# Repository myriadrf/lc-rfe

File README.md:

#  LibreCellular RFE Hardware

This repository contains the KiCAD design and manufacturing files for the LC-RFE hardware.

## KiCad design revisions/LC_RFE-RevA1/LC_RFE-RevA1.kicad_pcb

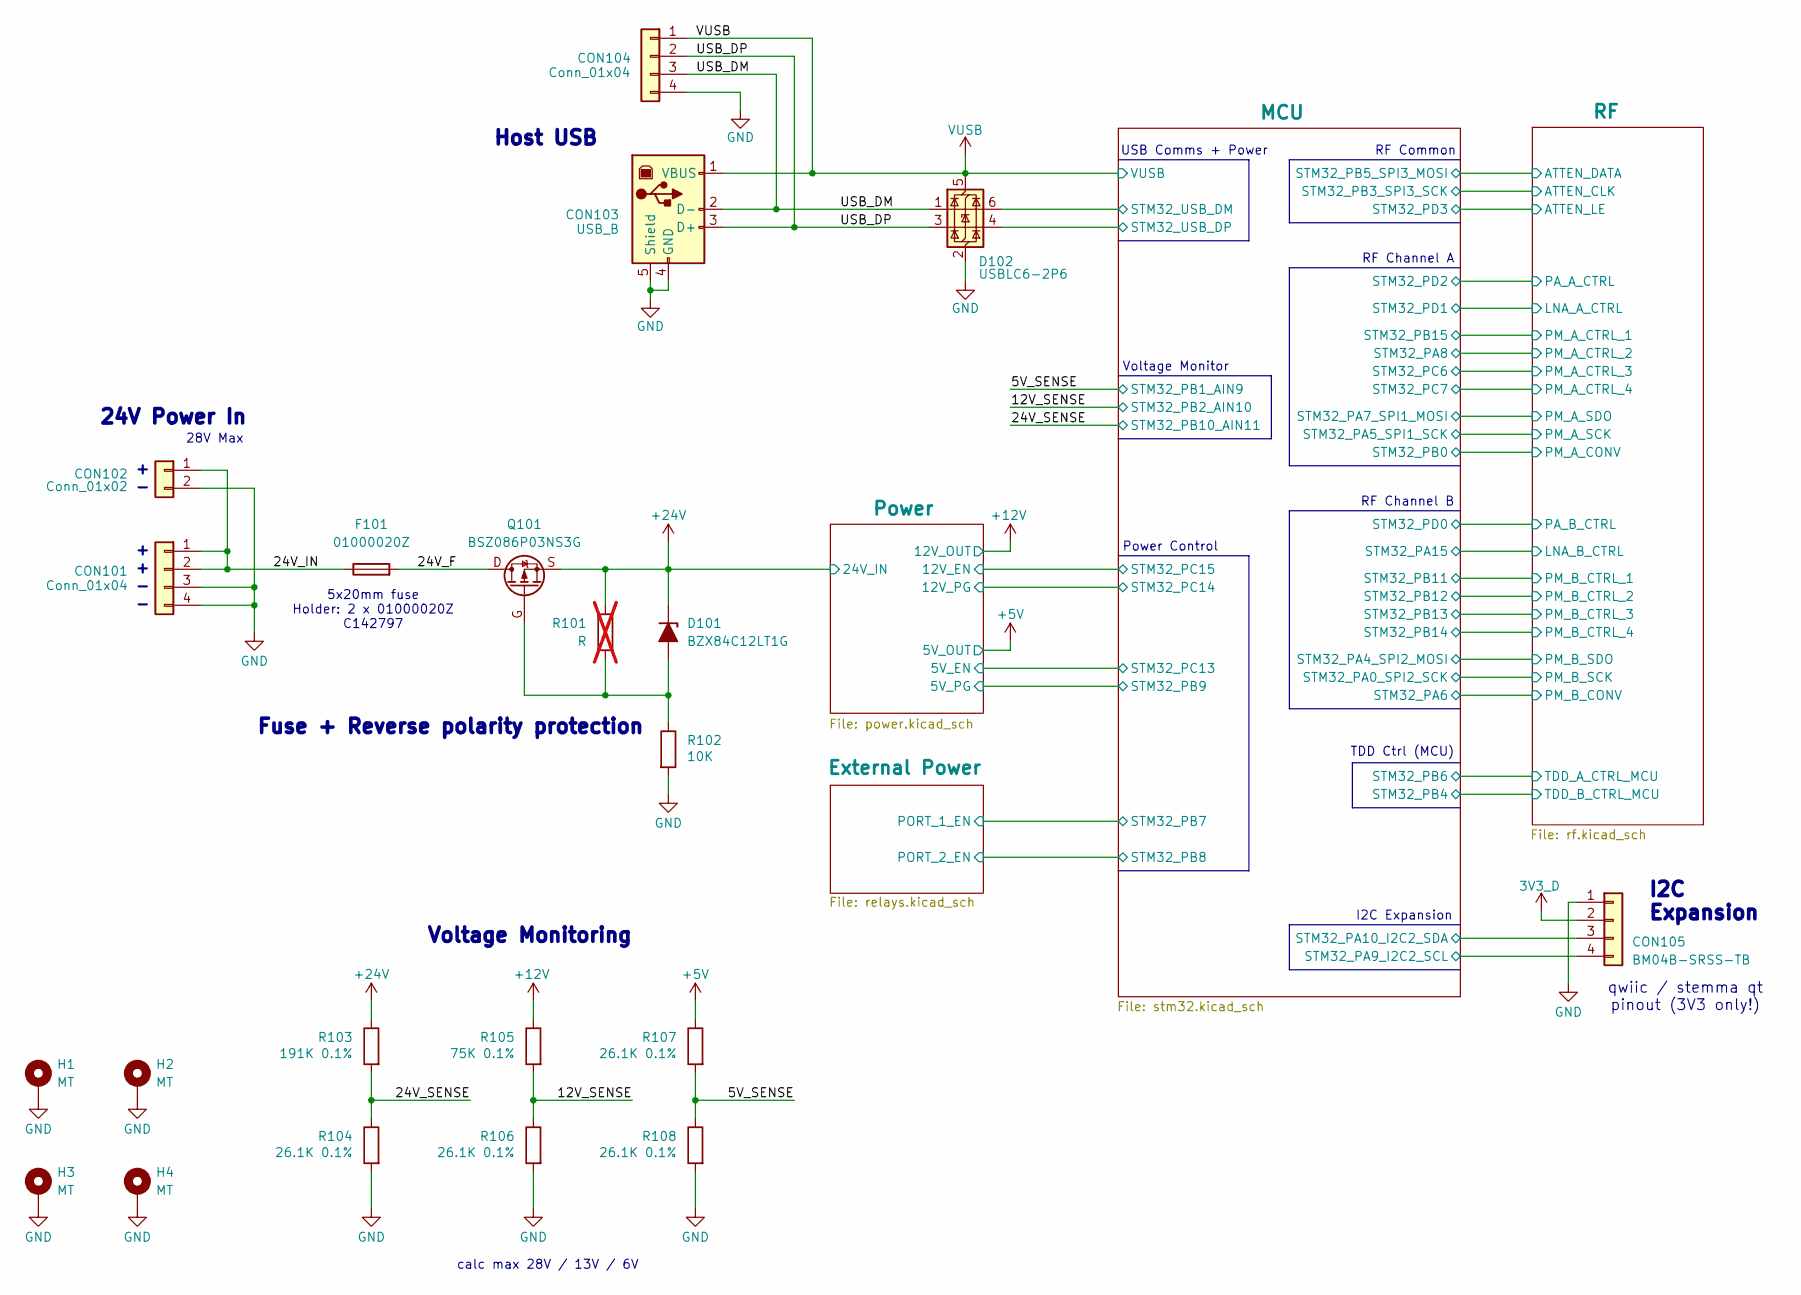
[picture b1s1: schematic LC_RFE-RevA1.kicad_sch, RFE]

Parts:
CON101: Conn_01x04; Dorabo_DB2ERC-2.5-4P-GN
CON102: Conn_01x02; Molex_KK-396_5273-02A_1x02_P3.96mm_Vertical
CON103: USB_B; Samtec_USBR-B-S-F-O-TH
CON104: Conn_01x04; Molex_KK-254_AE-6410-04A_1x04_P2.54mm_Vertical
CON105: BM04B-SRSS-TB
D101: BZX84C12LT1G; SOT-23; JLCASSY C82475
D102: USBLC6-2P6; SOT-666; JLCASSY C15999
F101: 01000020Z; Fuseholder_2x_Littelfuse_100_series_5x20mm; JLCASSY C142797
H1, H2, H3, H4: MT; MountingHole_3.2mm_M3_Pad_Via
Q101: BSZ086P03NS3G; TSDSON-8(3.3x3.3); JLCASSY C459171
R101: R; R_0402_1005Metric; not fitted
R102: 10K; R_0402_1005Metric; JLCASSY C2902636
R103: 191K 0.1%; R_0402_1005Metric; JLCASSY C2441163
R104, R106, R107, R108: 26.1K 0.1%; R_0402_1005Metric; JLCASSY C728557
R105: 75K 0.1%; R_0402_1005Metric; JLCASSY C319479

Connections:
3V3_D: CON105.2; also elsewhere on the board
+5V: R107.1; also elsewhere on the board
+12V: R105.1; also elsewhere on the board
+24V: D101.3 (K), Q101.S, R101.1, R103.1; also elsewhere on the board
/5V_SENSE: R107.2, R108.1; also elsewhere on the board
/12V_SENSE: R105.2, R106.1; also elsewhere on the board
/24V_F: F101.2, Q101.D
/24V_IN: CON101.1, CON101.2, CON102.1, F101.1
/24V_SENSE: R103.2, R104.1; also elsewhere on the board
/MCU/SCL: CON105.4; also elsewhere on the board
/MCU/SDA: CON105.3; also elsewhere on the board
/MCU/STM32_USB_DM: D102.6 (I/O1); also elsewhere on the board
/MCU/STM32_USB_DP: D102.4 (I/O2); also elsewhere on the board
/USB_DM: CON103.2 (D-), CON104.3, D102.1 (I/O1)
/USB_DP: CON103.3 (D+), CON104.2, D102.3 (I/O2)
GND: CON101.3, CON101.4, CON102.2, CON103.4 (GND), CON103.5 (Shield), CON104.4, CON105.1, D102.2 (GND), H1.1, H2.1, H3.1, H4.1, R102.2, R104.2, R106.2, R108.2; also elsewhere on the board
unnamed: D101.1 (A), Q101.G, R101.2, R102.1
VUSB: CON103.1 (VBUS), CON104.1, D102.5 (VBUS); also elsewhere on the board

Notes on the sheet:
5x20mm fuse Holder: 2 x 01000020Z C142797
I2C Expansion
Voltage Monitor
28V Max
calc max 28V / 13V / 6V
TDD Ctrl (MCU)
qwiic / stemma qt pinout (3V3 only!)
RF Common
Power Control
Voltage Monitoring
24V Power In
Host USB
RF Channel B
I2C Expansion
USB Comms + Power
Fuse + Reverse polarity protection
RF Channel A

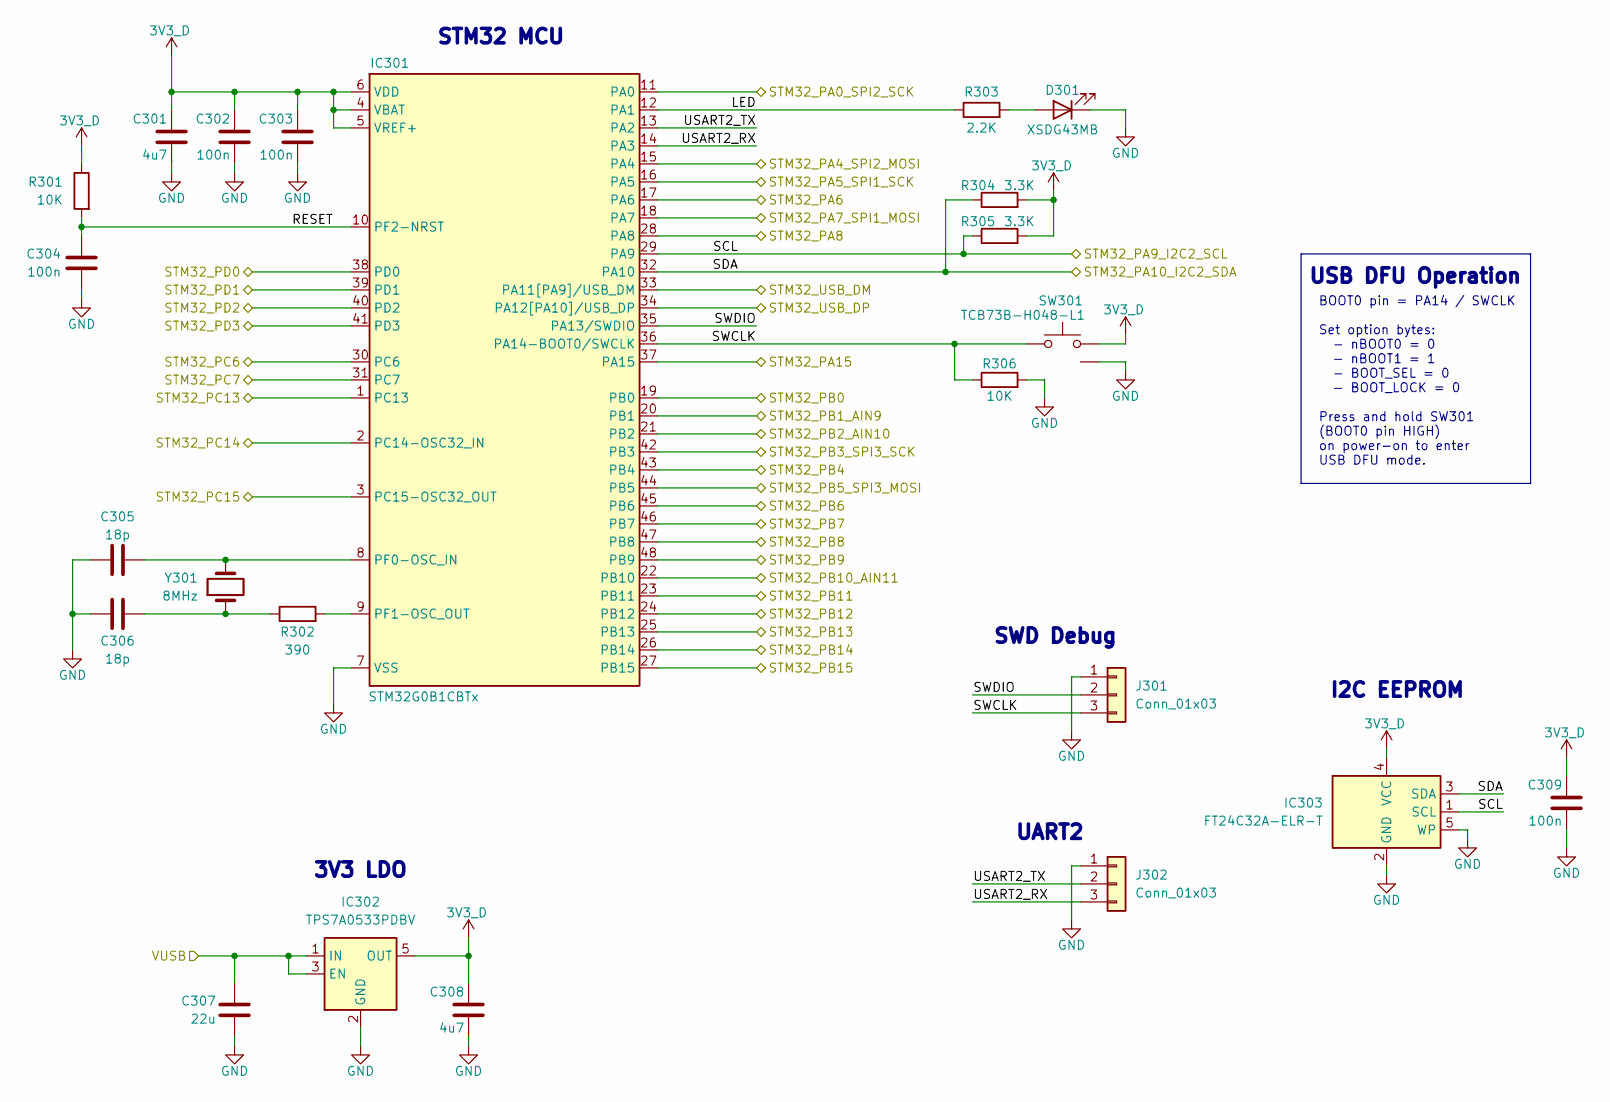
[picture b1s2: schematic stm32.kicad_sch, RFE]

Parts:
C301, C308: 4u7; C_0402_1005Metric; JLCASSY C23733
C302, C303, C304, C309: 100n; C_0402_1005Metric; JLCASSY C307331
C305, C306: 18p; C_0402_1005Metric; JLCASSY C1549
C307: 22u; C_1206_3216Metric; JLCASSY C478862
D301: XSDG43MB; LED_D3.0mm_Horizontal_O3.81mm_Z6.0mm; DIGIKEY 1497-1043-ND
IC301: STM32G0B1CBTx; LQFP-48_7x7mm_P0.5mm; JLCASSY C2847904
IC302: TPS7A0533PDBV; SOT-23-5; JLCASSY C493453
IC303: FT24C32A-ELR-T; SOT-23-5; JLCASSY C5263776
J301, J302: Conn_01x03; PinHeader_1x03_P2.54mm_Vertical
R301, R306: 10K; R_0402_1005Metric; JLCASSY C2902636
R302: 390; R_0402_1005Metric; JLCASSY C2906937
R303: 2.2K; R_0402_1005Metric; JLCASSY C25879
R304, R305: 3.3K; R_0402_1005Metric; JLCASSY C25890
SW301: TCB73B-H048-L1; PushButton-TCB73B-H048-L1; JLCASSY C2890354
Y301: 8MHz; Crystal_SMD_5032-2Pin_5.0x3.2mm; JLCASSY C3035202

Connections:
3V3_D: C301.1, C302.1, C303.1, C308.1, C309.1, IC301.4 (VBAT), IC301.5 (VREF+), IC301.6 (VDD), IC302.5 (OUT), IC303.4 (VCC), R301.1, R304.2, R305.2, SW301.2; also elsewhere on the board
/5V_SENSE: IC301.20 (PB1); also elsewhere on the board
/12V_SENSE: IC301.21 (PB2); also elsewhere on the board
/24V_SENSE: IC301.22 (PB10); also elsewhere on the board
/External Power/PORT_1_EN: IC301.46 (PB7); also elsewhere on the board
/External Power/PORT_2_EN: IC301.47 (PB8); also elsewhere on the board
/MCU/LED: IC301.12 (PA1), R303.1
/MCU/RESET: C304.1, IC301.10 (PF2-NRST), R301.2
/MCU/SCL: IC301.29 (PA9), IC303.1 (SCL), R305.1; also elsewhere on the board
/MCU/SDA: IC301.32 (PA10), IC303.3 (SDA), R304.1; also elsewhere on the board
/MCU/STM32_PA0_SPI2_SCK: IC301.11 (PA0); also elsewhere on the board
/MCU/STM32_PA4_SPI2_MOSI: IC301.15 (PA4); also elsewhere on the board
/MCU/STM32_PA5_SPI1_SCK: IC301.16 (PA5); also elsewhere on the board
/MCU/STM32_PA6: IC301.17 (PA6); also elsewhere on the board
/MCU/STM32_PA7_SPI1_MOSI: IC301.18 (PA7); also elsewhere on the board
/MCU/STM32_PA8: IC301.28 (PA8); also elsewhere on the board
/MCU/STM32_PA15: IC301.37 (PA15); also elsewhere on the board
/MCU/STM32_PB0: IC301.19 (PB0); also elsewhere on the board
/MCU/STM32_PB3_SPI3_SCK: IC301.42 (PB3); also elsewhere on the board
/MCU/STM32_PB4: IC301.43 (PB4); also elsewhere on the board
/MCU/STM32_PB5_SPI3_MOSI: IC301.44 (PB5); also elsewhere on the board
/MCU/STM32_PB6: IC301.45 (PB6); also elsewhere on the board
/MCU/STM32_PB9: IC301.48 (PB9); also elsewhere on the board
/MCU/STM32_PB11: IC301.23 (PB11); also elsewhere on the board
/MCU/STM32_PB12: IC301.24 (PB12); also elsewhere on the board
/MCU/STM32_PB13: IC301.25 (PB13); also elsewhere on the board
/MCU/STM32_PB14: IC301.26 (PB14); also elsewhere on the board
/MCU/STM32_PB15: IC301.27 (PB15); also elsewhere on the board
/MCU/STM32_PC6: IC301.30 (PC6); also elsewhere on the board
/MCU/STM32_PC7: IC301.31 (PC7); also elsewhere on the board
/MCU/STM32_PC13: IC301.1 (PC13); also elsewhere on the board
/MCU/STM32_PC14: IC301.2 (PC14-OSC32_IN); also elsewhere on the board
/MCU/STM32_PC15: IC301.3 (PC15-OSC32_OUT); also elsewhere on the board
/MCU/STM32_PD0: IC301.38 (PD0); also elsewhere on the board
/MCU/STM32_PD1: IC301.39 (PD1); also elsewhere on the board
/MCU/STM32_PD2: IC301.40 (PD2); also elsewhere on the board
/MCU/STM32_PD3: IC301.41 (PD3); also elsewhere on the board
/MCU/STM32_USB_DM: IC301.33 (PA11[PA9]/USB_DM); also elsewhere on the board
/MCU/STM32_USB_DP: IC301.34 (PA12[PA10]/USB_DP); also elsewhere on the board
/MCU/SWCLK: IC301.36 (PA14-BOOT0/SWCLK), J301.3, R306.1, SW301.1
/MCU/SWDIO: IC301.35 (PA13/SWDIO), J301.2
/MCU/USART2_RX: IC301.14 (PA3), J302.3
/MCU/USART2_TX: IC301.13 (PA2), J302.2
GND: C301.2, C302.2, C303.2, C304.2, C305.1, C306.1, C307.2, C308.2, C309.2, D301.1 (K), IC301.7 (VSS), IC302.2 (GND), IC303.2 (GND), IC303.5 (WP), J301.1, J302.1, R306.2, SW301.3; also elsewhere on the board
unnamed: C306.2, R302.1, Y301.1
unnamed: D301.2 (A), R303.2
unnamed: C305.2, IC301.8 (PF0-OSC_IN), Y301.2
unnamed: IC301.9 (PF1-OSC_OUT), R302.2
VUSB: C307.1, IC302.1 (IN), IC302.3 (EN); also elsewhere on the board

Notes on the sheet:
I2C EEPROM
3V3 LDO
BOOT0 pin = PA14 / SWCLK Set option bytes: - nBOOT0 = 0 - nBOOT1 = 1 - BOOT_SEL = 0 - BOOT_LOCK = 0 Press and hold SW301 (BOOT0 pin HIGH) on power-on to enter USB DFU mode.
UART2
SWD Debug
USB DFU Operation
STM32 MCU

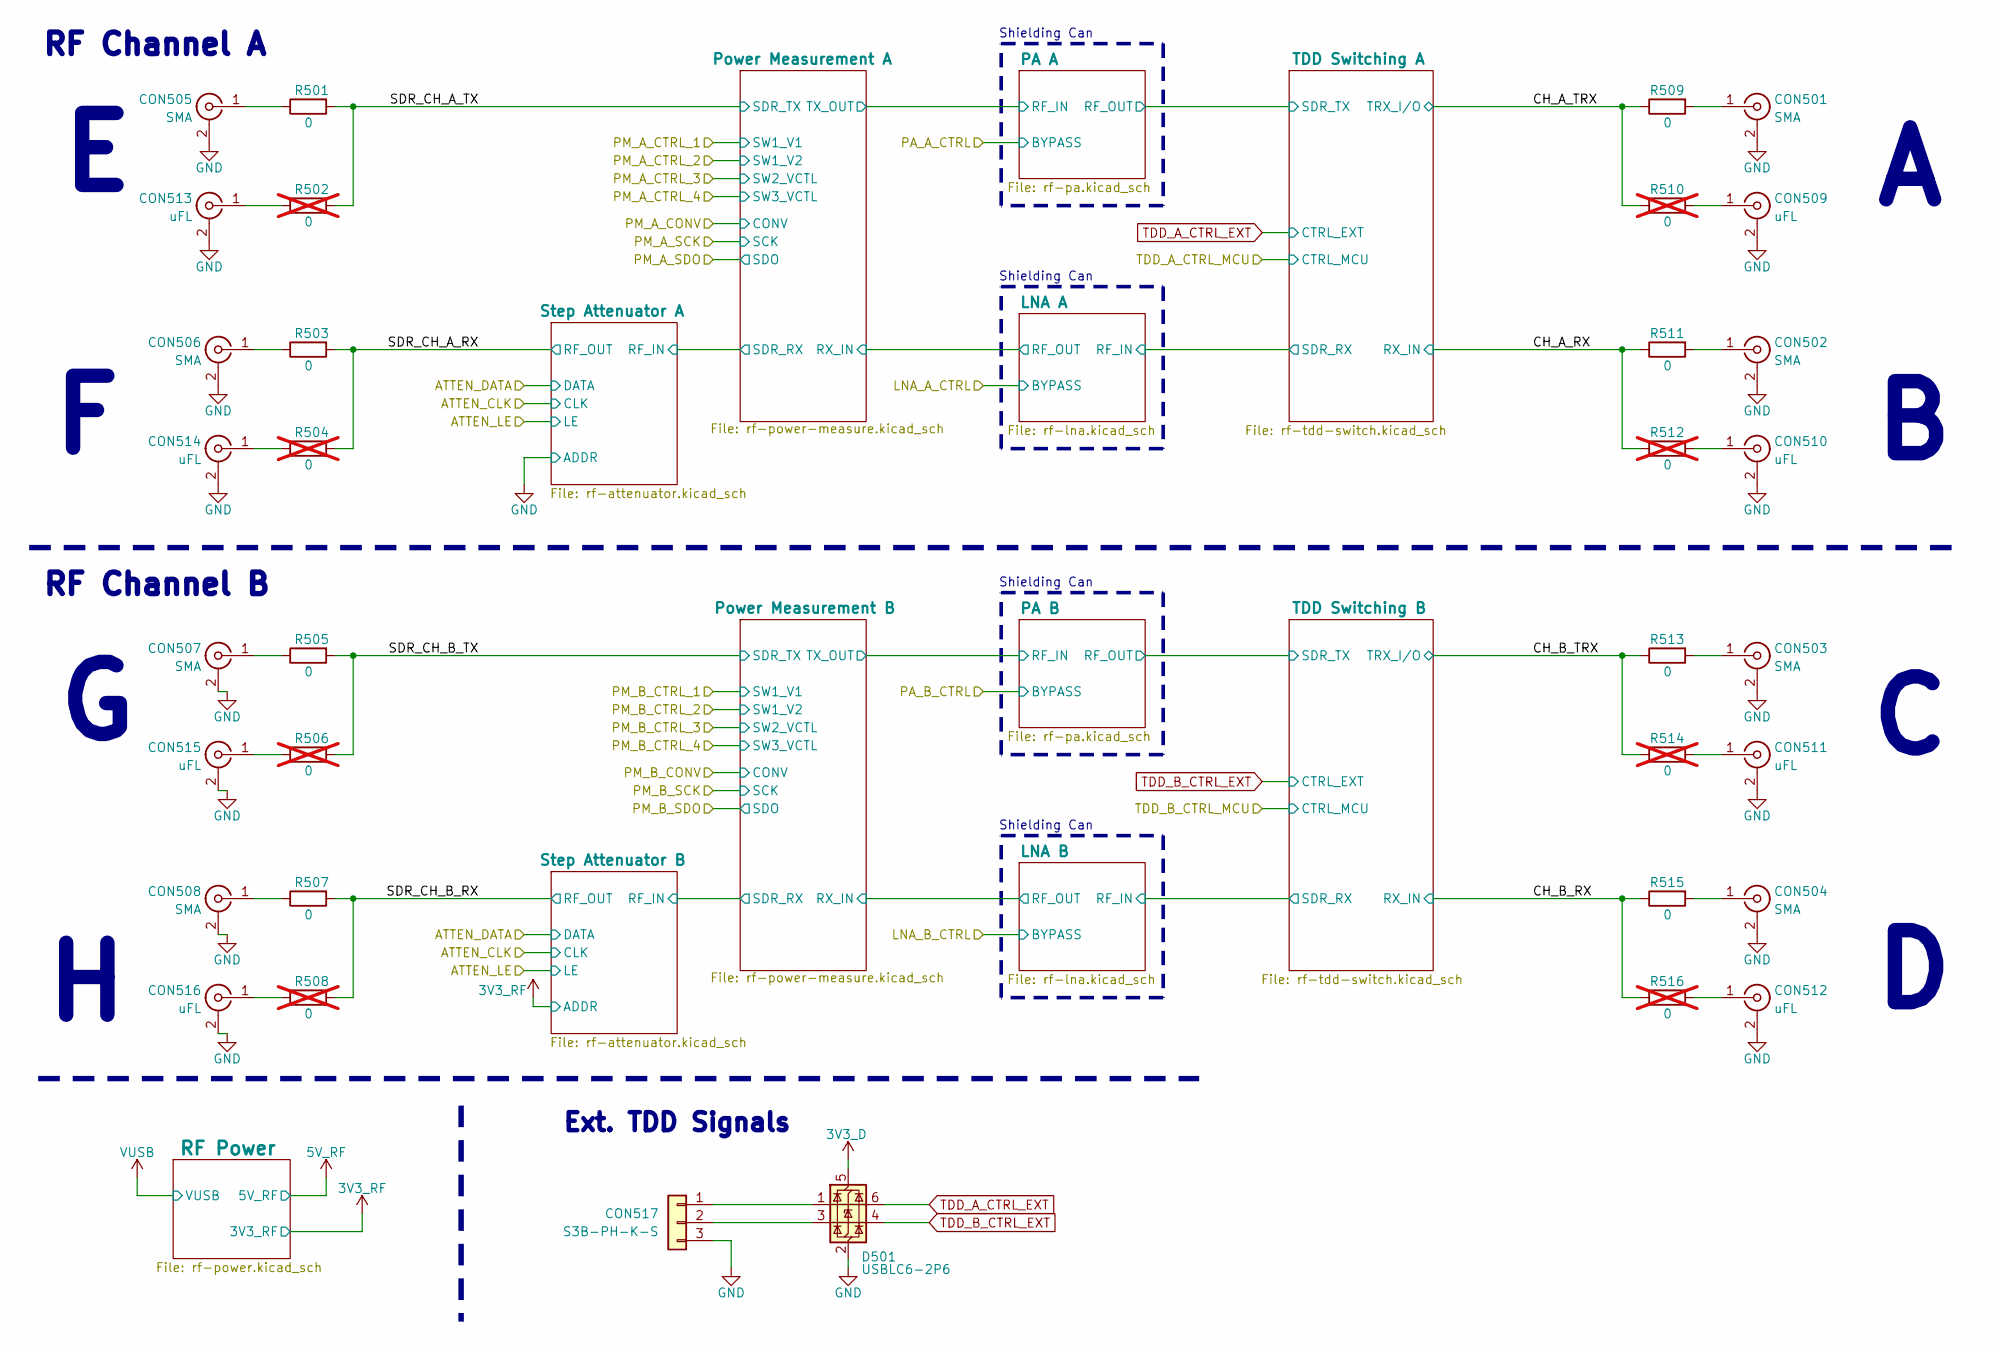
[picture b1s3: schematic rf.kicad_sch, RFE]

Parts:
CON501, CON502, CON503, CON504, CON505, CON506, CON507, CON508: SMA; Samtec_SMA-J-P-H-RA-TH1
CON509, CON510, CON511, CON512, CON513, CON514, CON515, CON516: uFL; Molex_734120110; MPN HC-RF-IPEX0303-01; JLCASSY C2894919
CON517: S3B-PH-K-S; Connector-2mm-1x3P_S3B-PH-K-S
D501: USBLC6-2P6; SOT-666; JLCASSY C15999
R501, R503, R505, R507, R509, R511, R513, R515: 0; 0201-SQUARE; MPN RC0201FR-070RL; JLCASSY C106227
R502, R504, R506, R508, R510, R512, R514, R516: 0; 0201-SQUARE; MPN RC0201FR-070RL; JLCASSY C106227; not fitted

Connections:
3V3_D: D501.5 (VBUS); also elsewhere on the board
/RF/CH_A_RX: R511.1, R512.1; also elsewhere on the board
/RF/CH_A_TRX: R509.1, R510.1; also elsewhere on the board
/RF/CH_B_RX: R515.1, R516.1; also elsewhere on the board
/RF/CH_B_TRX: R513.1, R514.1; also elsewhere on the board
/RF/SDR_CH_A_RX: R503.2, R504.2; also elsewhere on the board
/RF/SDR_CH_A_TX: R501.2, R502.2; also elsewhere on the board
/RF/SDR_CH_B_RX: R507.2, R508.2; also elsewhere on the board
/RF/SDR_CH_B_TX: R505.2, R506.2; also elsewhere on the board
GND: CON501.2 (Ext), CON502.2 (Ext), CON503.2 (Ext), CON504.2 (Ext), CON505.2 (Ext), CON506.2 (Ext), CON507.2 (Ext), CON508.2 (Ext), CON509.2 (Ext), CON510.2 (Ext), CON511.2 (Ext), CON512.2 (Ext), CON513.2 (Ext), CON514.2 (Ext), CON515.2 (Ext), CON516.2 (Ext), CON517.3, D501.2 (GND); also elsewhere on the board
unnamed: CON501.1 (In), R509.2
unnamed: CON502.1 (In), R511.2
unnamed: CON503.1 (In), R513.2
unnamed: CON504.1 (In), R515.2
unnamed: CON505.1 (In), R501.1
unnamed: CON506.1 (In), R503.1
unnamed: CON507.1 (In), R505.1
unnamed: CON508.1 (In), R507.1
unnamed: CON509.1 (In), R510.2
unnamed: CON510.1 (In), R512.2
unnamed: CON511.1 (In), R514.2
unnamed: CON512.1 (In), R516.2
unnamed: CON513.1 (In), R502.1
unnamed: CON514.1 (In), R504.1
unnamed: CON515.1 (In), R506.1
unnamed: CON516.1 (In), R508.1
unnamed: CON517.1, D501.1 (I/O1)
unnamed: CON517.2, D501.3 (I/O2)
TDD_A_CTRL_EXT: D501.6 (I/O1); also elsewhere on the board
TDD_B_CTRL_EXT: D501.4 (I/O2); also elsewhere on the board

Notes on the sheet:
Ext. TDD Signals
Shielding Can
RF Channel B
RF Channel A

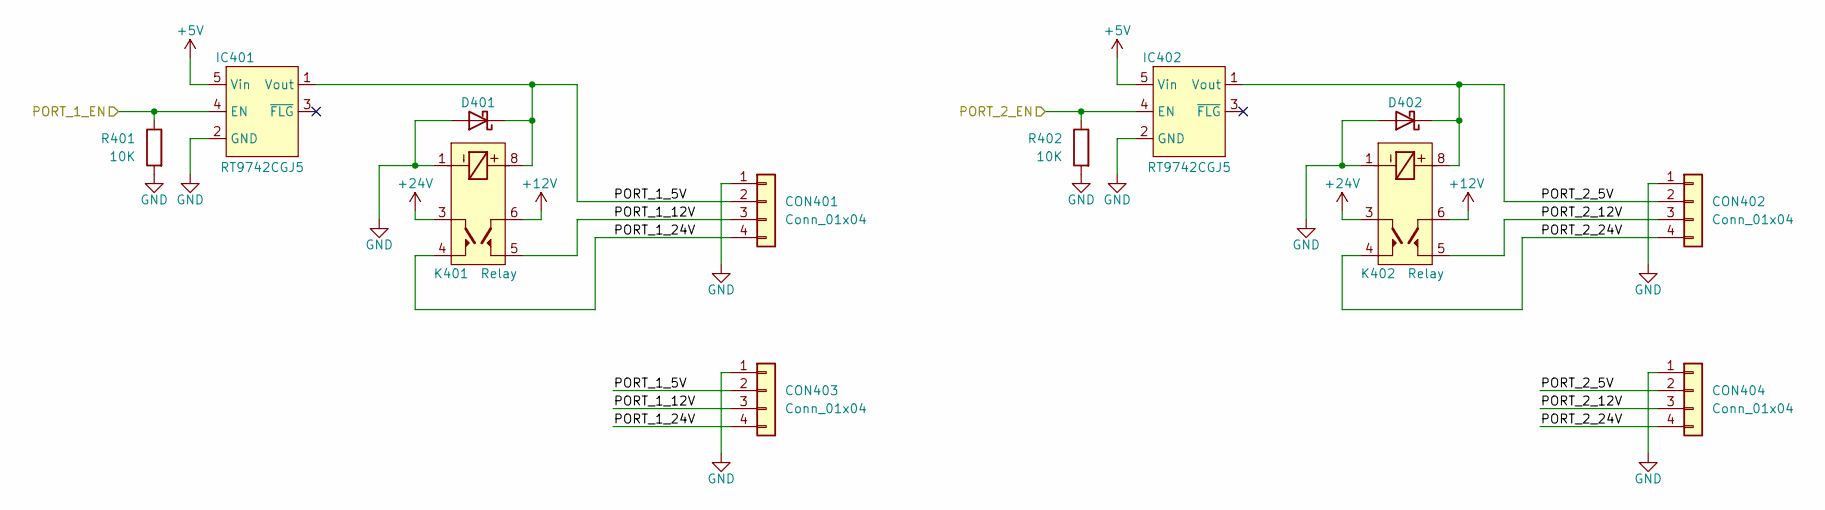
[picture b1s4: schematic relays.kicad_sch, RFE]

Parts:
CON401, CON402: Conn_01x04; Dorabo_DB2ERC-2.5-4P-GN
CON403, CON404: Conn_01x04; Molex_KK-254_AE-6410-04A_1x04_P2.54mm_Vertical
D401, D402: D_Schottky; D_SOD-323_HandSoldering; JLCASSY C191023
IC401, IC402: RT9742CGJ5; TSOT-23-5; JLCASSY C250546
K401, K402: Relay; Omron_P6B-26P+G6B-2214
R401, R402: 10K; R_0402_1005Metric; JLCASSY C2902636

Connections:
+5V: IC401.5 (Vin), IC402.5 (Vin); also elsewhere on the board
+12V: K401.6, K402.6; also elsewhere on the board
+24V: K401.3, K402.3; also elsewhere on the board
/External Power/PORT_1_5V: CON401.2, CON403.2, D401.1 (K), IC401.1 (Vout), K401.8
/External Power/PORT_1_12V: CON401.3, CON403.3, K401.5
/External Power/PORT_1_24V: CON401.4, CON403.4, K401.4
/External Power/PORT_1_EN: IC401.4 (EN), R401.1; also elsewhere on the board
/External Power/PORT_2_5V: CON402.2, CON404.2, D402.1 (K), IC402.1 (Vout), K402.8
/External Power/PORT_2_12V: CON402.3, CON404.3, K402.5
/External Power/PORT_2_24V: CON402.4, CON404.4, K402.4
/External Power/PORT_2_EN: IC402.4 (EN), R402.1; also elsewhere on the board
GND: CON401.1, CON402.1, CON403.1, CON404.1, D401.2 (A), D402.2 (A), IC401.2 (GND), IC402.2 (GND), K401.1, K402.1, R401.2, R402.2; also elsewhere on the board

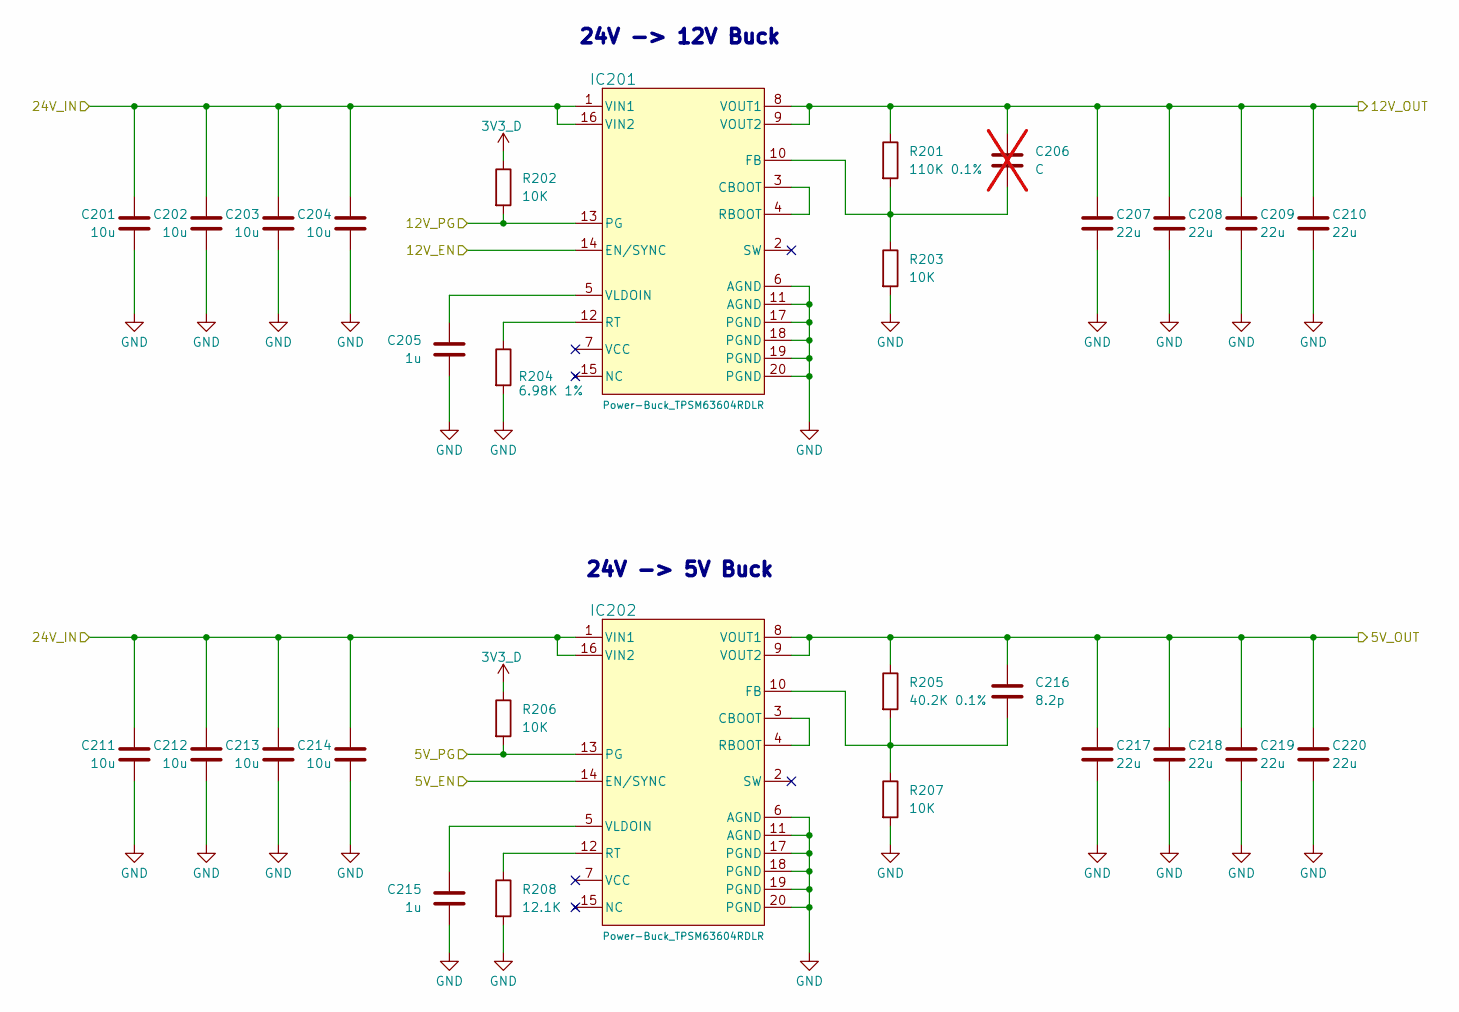
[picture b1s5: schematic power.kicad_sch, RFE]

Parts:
C201, C202, C203, C204, C211, C212, C213, C214: 10u; C_1210_3225Metric; JLCASSY C597578
C205, C215: 1u; C_0603_1608Metric; JLCASSY C519560
C206: C; C_0402_1005Metric; not fitted
C207, C208, C209, C210, C217, C218, C219, C220: 22u; C_1206_3216Metric; JLCASSY C478862
C216: 8.2p; C_0402_1005Metric; JLCASSY C1579
IC201, IC202: Power-Buck_TPSM63604RDLR; B3QFN-20(5.0x5.5)-RDL0020A; JLCASSY C5219289
R201: 110K 0.1%; R_0402_1005Metric; JLCASSY C517659
R202, R203, R206, R207: 10K; R_0402_1005Metric; JLCASSY C2902636
R204: 6.98K 1%; R_0402_1005Metric; JLCASSY C47500
R205: 40.2K 0.1%; R_0402_1005Metric; JLCASSY C852775
R208: 12.1K; R_0402_1005Metric; JLCASSY C281773

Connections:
3V3_D: R202.1, R206.1; also elsewhere on the board
+5V: C216.1, C217.1, C218.1, C219.1, C220.1, IC202.8 (VOUT1), IC202.9 (VOUT2), R205.1; also elsewhere on the board
+12V: C206.1, C207.1, C208.1, C209.1, C210.1, IC201.8 (VOUT1), IC201.9 (VOUT2), R201.1; also elsewhere on the board
+24V: C201.1, C202.1, C203.1, C204.1, C211.1, C212.1, C213.1, C214.1, IC201.1 (VIN1), IC201.16 (VIN2), IC202.1 (VIN1), IC202.16 (VIN2); also elsewhere on the board
/MCU/STM32_PB9: IC202.13 (PG), R206.2; also elsewhere on the board
/MCU/STM32_PC13: IC202.14 (EN/SYNC); also elsewhere on the board
/MCU/STM32_PC14: IC201.13 (PG), R202.2; also elsewhere on the board
/MCU/STM32_PC15: IC201.14 (EN/SYNC); also elsewhere on the board
GND: C201.2, C202.2, C203.2, C204.2, C205.2, C207.2, C208.2, C209.2, C210.2, C211.2, C212.2, C213.2, C214.2, C215.2, C217.2, C218.2, C219.2, C220.2, IC201.6 (AGND), IC201.11 (AGND), IC201.17 (PGND), IC201.18 (PGND), IC201.19 (PGND), IC201.20 (PGND), IC202.6 (AGND), IC202.11 (AGND), IC202.17 (PGND), IC202.18 (PGND), IC202.19 (PGND), IC202.20 (PGND), R203.2, R204.2, R207.2, R208.2; also elsewhere on the board
unnamed: IC201.3 (CBOOT), IC201.4 (RBOOT)
unnamed: C206.2, IC201.10 (FB), R201.2, R203.1
unnamed: IC201.12 (RT), R204.1
unnamed: C205.1, IC201.5 (VLDOIN)
unnamed: IC202.3 (CBOOT), IC202.4 (RBOOT)
unnamed: C216.2, IC202.10 (FB), R205.2, R207.1
unnamed: IC202.12 (RT), R208.1
unnamed: C215.1, IC202.5 (VLDOIN)

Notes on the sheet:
24V -> 5V Buck
24V -> 12V Buck

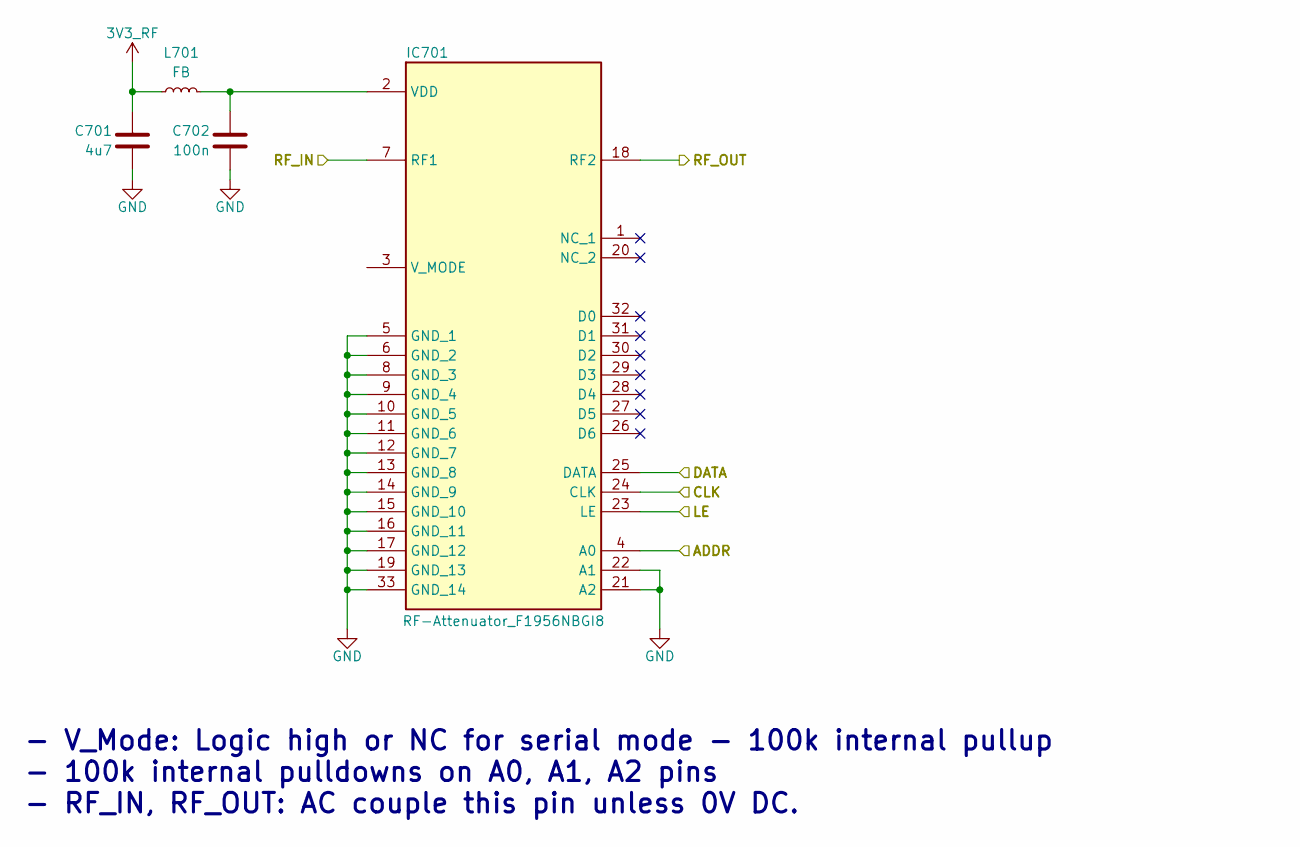
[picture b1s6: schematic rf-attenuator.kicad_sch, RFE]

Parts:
C701: 4u7; C_0402_1005Metric; JLCASSY C23733
C702: 100n; C_0402_1005Metric; JLCASSY C307331
IC701: RF-Attenuator_F1956NBGI8; QFN50P500X500X80-33N-D; Manufacturer_Part_Number F1956NBGI8; Mouser Part Number 972-F1956NBGI8
L701: FB; L_0402_1005Metric; JLCASSY C491491

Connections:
3V3_RF: C701.1, L701.1; also elsewhere on the board
/MCU/STM32_PB3_SPI3_SCK: IC701.24 (CLK); also elsewhere on the board
/MCU/STM32_PB5_SPI3_MOSI: IC701.25 (DATA); also elsewhere on the board
/MCU/STM32_PD3: IC701.23 (LE); also elsewhere on the board
/RF/Power Measurement A/SDR_RX: IC701.7 (RF1); also elsewhere on the board
/RF/SDR_CH_A_RX: IC701.18 (RF2); also elsewhere on the board
GND: C701.2, C702.2, IC701.4 (A0), IC701.5 (GND_1), IC701.6 (GND_2), IC701.8 (GND_3), IC701.9 (GND_4), IC701.10 (GND_5), IC701.11 (GND_6), IC701.12 (GND_7), IC701.13 (GND_8), IC701.14 (GND_9), IC701.15 (GND_10), IC701.16 (GND_11), IC701.17 (GND_12), IC701.19 (GND_13), IC701.21 (A2), IC701.22 (A1), IC701.33 (GND_14); also elsewhere on the board
unnamed: C702.1, IC701.2 (VDD), L701.2

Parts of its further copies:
C801: 4u7; C_0402_1005Metric; JLCASSY C23733
C802: 100n; C_0402_1005Metric; JLCASSY C307331
IC801: RF-Attenuator_F1956NBGI8; QFN50P500X500X80-33N-D; Manufacturer_Part_Number F1956NBGI8; Mouser Part Number 972-F1956NBGI8
L801: FB; L_0402_1005Metric; JLCASSY C491491

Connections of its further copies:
3V3_RF: C801.1, IC801.4 (A0), L801.1; also elsewhere on the board
/MCU/STM32_PB3_SPI3_SCK: IC801.24 (CLK); also elsewhere on the board
/MCU/STM32_PB5_SPI3_MOSI: IC801.25 (DATA); also elsewhere on the board
/MCU/STM32_PD3: IC801.23 (LE); also elsewhere on the board
/RF/Power Measurement B/SDR_RX: IC801.7 (RF1); also elsewhere on the board
/RF/SDR_CH_B_RX: IC801.18 (RF2); also elsewhere on the board
GND: C801.2, C802.2, IC801.5 (GND_1), IC801.6 (GND_2), IC801.8 (GND_3), IC801.9 (GND_4), IC801.10 (GND_5), IC801.11 (GND_6), IC801.12 (GND_7), IC801.13 (GND_8), IC801.14 (GND_9), IC801.15 (GND_10), IC801.16 (GND_11), IC801.17 (GND_12), IC801.19 (GND_13), IC801.21 (A2), IC801.22 (A1), IC801.33 (GND_14); also elsewhere on the board
unnamed: C802.1, IC801.2 (VDD), L801.2

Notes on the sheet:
- V_Mode: Logic high or NC for serial mode - 100k internal pullup - 100k internal pulldowns on A0, A1, A2 pins - RF_IN, RF_OUT: AC couple this pin unless 0V DC.
